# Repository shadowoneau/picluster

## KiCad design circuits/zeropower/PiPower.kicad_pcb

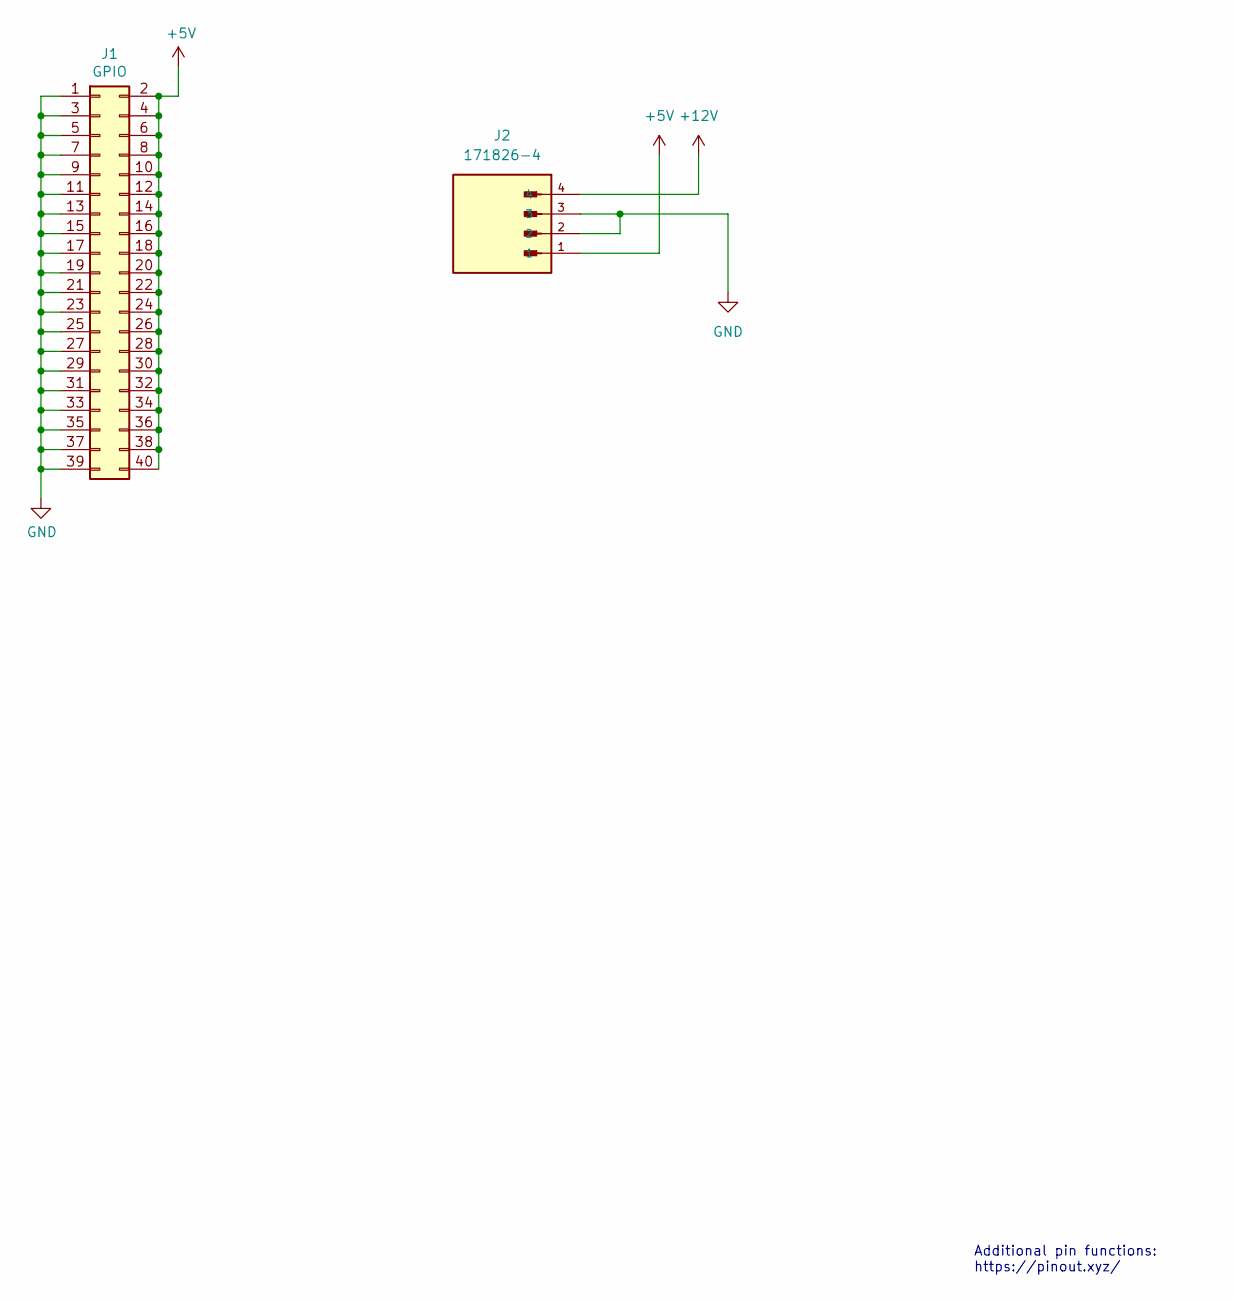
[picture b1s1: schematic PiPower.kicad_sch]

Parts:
J1: GPIO; PinSocket_2x20_P2.54mm_Vertical
J2: 171826-4; TE_171826-4

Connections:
+5V: J1.2, J1.4, J1.6, J1.8, J1.10, J1.12, J1.14, J1.16, J1.18, J1.20, J1.22, J1.24, J1.26, J1.28, J1.30, J1.32, J1.34, J1.36, J1.38, J1.40, J2.1
+12V: J2.4
GND: J1.1, J1.3, J1.5, J1.7, J1.9, J1.11, J1.13, J1.15, J1.17, J1.19, J1.21, J1.23, J1.25, J1.27, J1.29, J1.31, J1.33, J1.35, J1.37, J1.39, J2.2, J2.3

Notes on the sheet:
Additional pin functions: https://pinout.xyz/

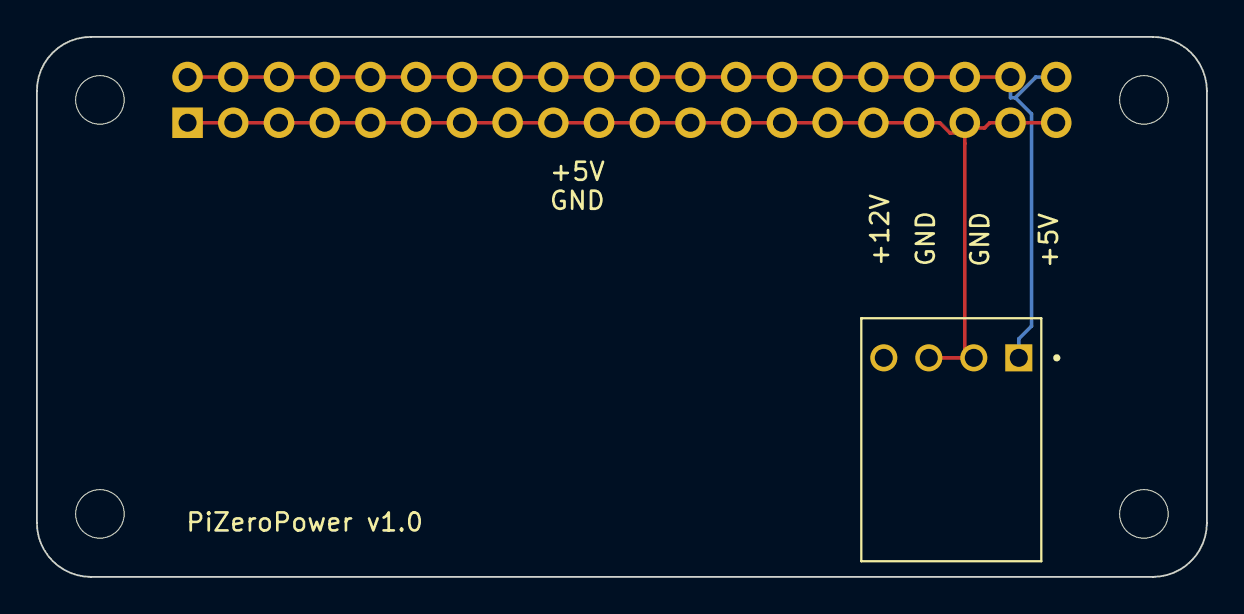
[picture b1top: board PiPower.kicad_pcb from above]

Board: 2 copper layers, 65.0 x 30.0 mm, 6 parts (1 on the bottom side), 2 nets.

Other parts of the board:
MH1, MH2, MH3, MH4: MountingHole_2.7mm_M2.5

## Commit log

2024-03-29 Add .gitignore for circuits designed with KiCad
2024-03-29 Init import of Pi power module in PiZero form factor
2024-03-29 Add backup directory
2024-03-29 Add silkscreen boardname and voltages
